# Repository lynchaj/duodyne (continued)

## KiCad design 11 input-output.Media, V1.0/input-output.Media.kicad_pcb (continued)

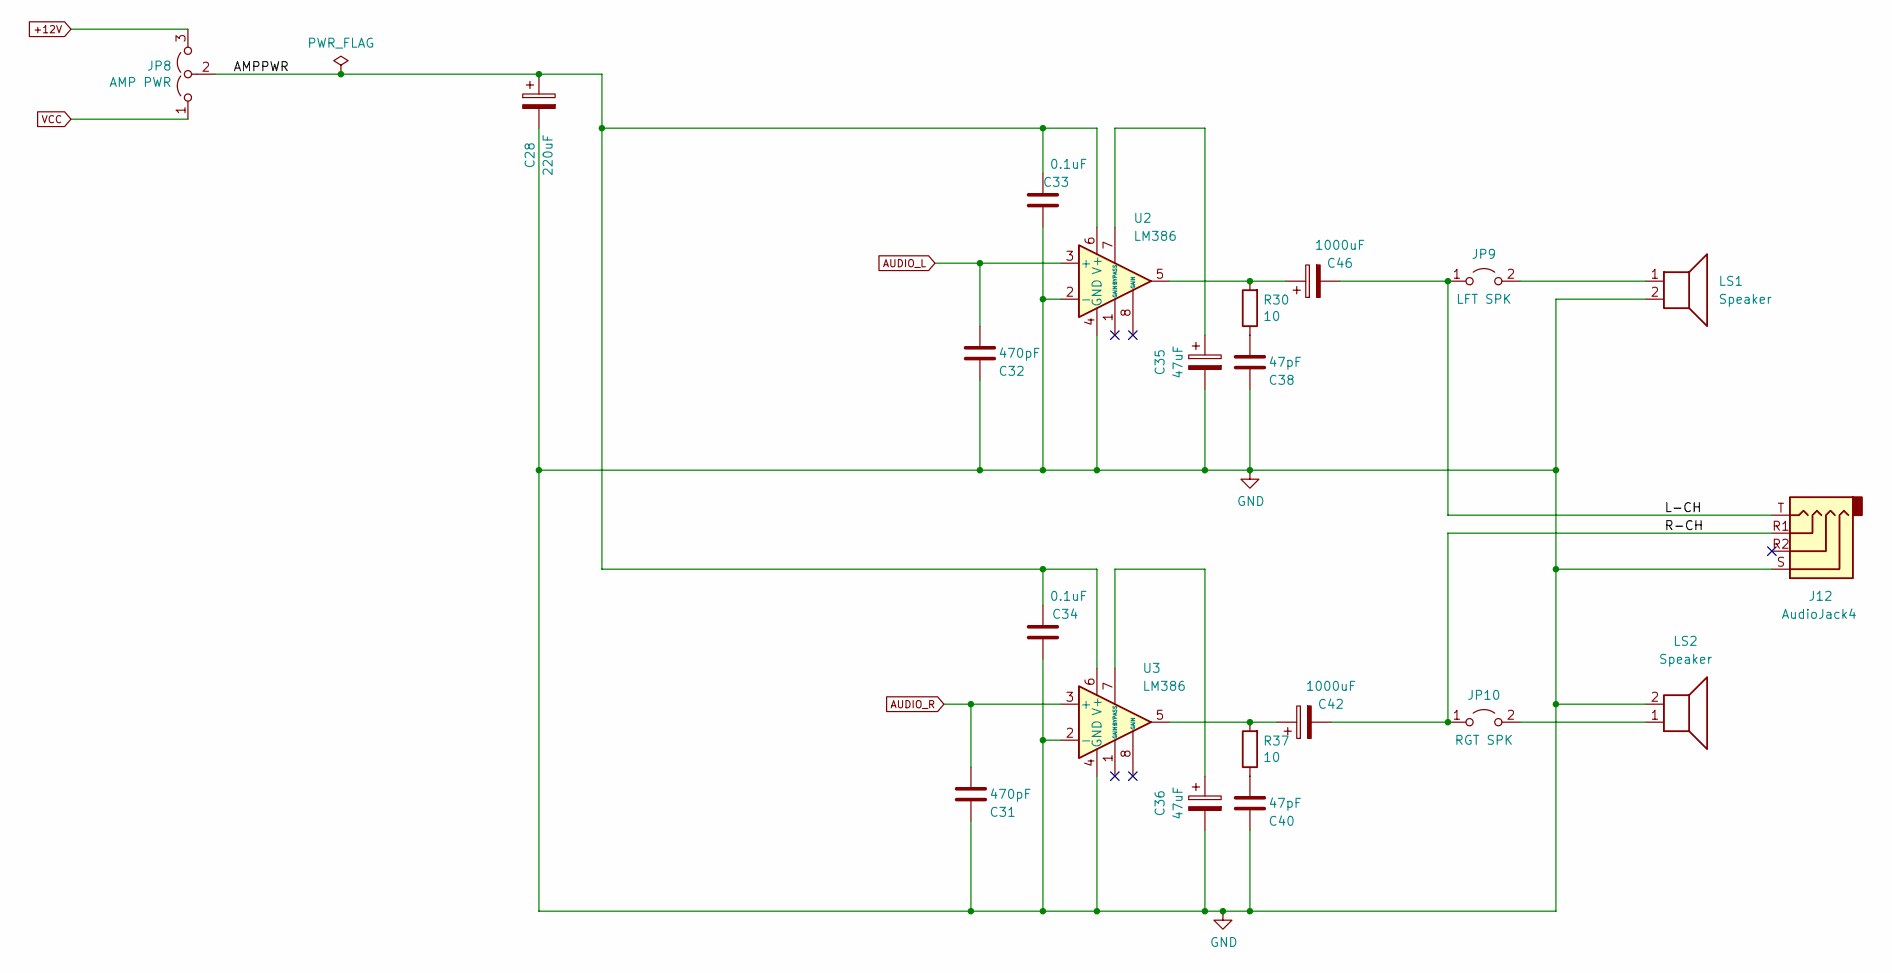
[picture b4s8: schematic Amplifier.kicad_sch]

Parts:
C28: 220uF; CP_Radial_D8.0mm_P2.50mm
C31, C32: 470pF; C_Disc_D3.8mm_W2.6mm_P2.50mm
C33, C34: 0.1uF; C_Disc_D5.0mm_W2.5mm_P5.00mm
C35, C36: 47uF; CP_Radial_D5.0mm_P2.50mm
C38, C40: 47pF; C_Disc_D3.8mm_W2.6mm_P2.50mm
C42, C46: 1000uF; CP_Radial_D8.0mm_P2.50mm
J12: AudioJack4; Jack_3.5mm_PJ320E_Horizontal
JP8: AMP PWR; PinHeader_1x03_P2.54mm_Vertical
JP9: LFT SPK; PinHeader_1x02_P2.54mm_Vertical
JP10: RGT SPK; PinHeader_1x02_P2.54mm_Vertical
LS1, LS2: Speaker; Jameco PCB Speaker 30mm 135722
R30, R37: 10; R_Axial_DIN0207_L6.3mm_D2.5mm_P10.16mm_Horizontal
U2, U3: LM386; DIP-8_W7.62mm

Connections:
+12V: JP8.3 (B); also elsewhere on the board
/Amplifier/AMPPWR: C28.1, C33.2, C34.2, JP8.2 (C), U2.6 (V+), U3.6 (V+)
/Amplifier/L-CH: C46.2, J12.T, JP9.1 (A)
/Amplifier/R-CH: C42.2, J12.R1, JP10.1 (A)
AUDIO_L: C32.1, U2.3 (+); also elsewhere on the board
AUDIO_R: C31.1, U3.3 (+); also elsewhere on the board
GND: C28.2, C31.2, C32.2, C33.1, C34.1, C35.2, C36.2, C38.2, C40.2, J12.S, LS1.2, LS2.2, U2.2 (-), U2.4 (GND), U3.2 (-), U3.4 (GND); also elsewhere on the board
unnamed: C35.1, U2.7 (BYPASS)
unnamed: C36.1, U3.7 (BYPASS)
unnamed: C38.1, R30.1
unnamed: C40.1, R37.1
unnamed: C42.1, R37.2, U3.5
unnamed: C46.1, R30.2, U2.5
unnamed: JP9.2 (B), LS1.1
unnamed: JP10.2 (B), LS2.1
VCC: JP8.1 (A); also elsewhere on the board

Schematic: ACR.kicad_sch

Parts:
D2, D4: LED; LED_D3.0mm_Horizontal_O3.81mm_Z2.0mm
R6, R10: 470; R_Axial_DIN0207_L6.3mm_D2.5mm_P7.62mm_Horizontal
U4: 74LS06; DIP-14_W7.62mm
U9: 74LS174; DIP-16_W7.62mm
U24: 74LS04; DIP-14_W7.62mm

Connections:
/ACR/STATUS-PSG: U4.11, U9.10 (Q3)
/ACR/STATUS-VDP: U4.3, U9.7 (Q2)
ACR5: U9.15 (Q5); also elsewhere on the board
GND: U9.8 (GND); also elsewhere on the board
unnamed: D2.1 (K), U4.4
unnamed: D2.2 (A), R6.1
unnamed: D4.1 (K), U4.10
unnamed: D4.2 (A), R10.1
unnamed: U9.2 (Q0), U24.5
VCC: R6.2, R10.2, U9.16 (VCC); also elsewhere on the board
bD0: U9.3 (D0); also elsewhere on the board
bD1: U9.4 (D1); also elsewhere on the board
bD2: U9.6 (D2); also elsewhere on the board
bD3: U9.11 (D3); also elsewhere on the board
bD4: U9.13 (D4); also elsewhere on the board
bD5: U9.14 (D5); also elsewhere on the board
~CS_ACR_WR: U9.9 (Cp); also elsewhere on the board
~RESAY3: U9.12 (Q4); also elsewhere on the board
~RESVDP: U24.6; also elsewhere on the board
~bRESET: U9.1 (~Mr); also elsewhere on the board

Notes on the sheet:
NOTE: ~{RESVDP} DEFAULTS TO HIGH LATCH Q0 MUST BE SET TO HIGH TO RESET V9938 OR V9958 (bD0=1)

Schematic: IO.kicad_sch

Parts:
RN1: 10K; R_Array_SIP9
SW1: IO PORT ADDR; PinHeader_2x05_P2.54mm_Vertical
U21: 74LS688; DIP-20_W7.62mm

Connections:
GND: U21.10 (GND); also elsewhere on the board
unnamed: RN1.2 (R1), SW1.1, U21.18 (R7)
unnamed: RN1.3 (R2), SW1.3, U21.16 (R6)
unnamed: RN1.4 (R3), SW1.5, U21.14 (R5)
unnamed: RN1.5 (R4), SW1.7, U21.12 (R4)
unnamed: RN1.6 (R5), SW1.9, U21.9 (R3)
unnamed: RN1.9 (R8), U21.3 (R0), U21.4 (P1), U21.5 (R1), U21.6 (P2), U21.7 (R2)
VCC: RN1.1 (common), U21.20 (VCC); also elsewhere on the board
ZERO: SW1.2, SW1.4, SW1.6, SW1.8, SW1.10; also elsewhere on the board
bA3: U21.8 (P3); also elsewhere on the board
bA4: U21.11 (P4); also elsewhere on the board
bA5: U21.13 (P5); also elsewhere on the board
bA6: U21.15 (P6); also elsewhere on the board
bA7: U21.17 (P7); also elsewhere on the board
~CS_MEDIA: U21.19 (P=R); also elsewhere on the board
~bIORQ: U21.1 (G); also elsewhere on the board
~bM1: U21.2 (P0); also elsewhere on the board

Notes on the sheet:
SET IO PORT
Note: IO Address Port $A0-$A7 1-2 =off - A7 (high) 3-4 =on - A6 (low) 5-6 =on - A5 (low) 7-8 =off - A4 (high) 9-10 =on - A3 (low)
IO SELECTION CIRCUIT
Note: Inhibit Board Operation During Interrupts ~{M1} = low, ~{IORQ} = low

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
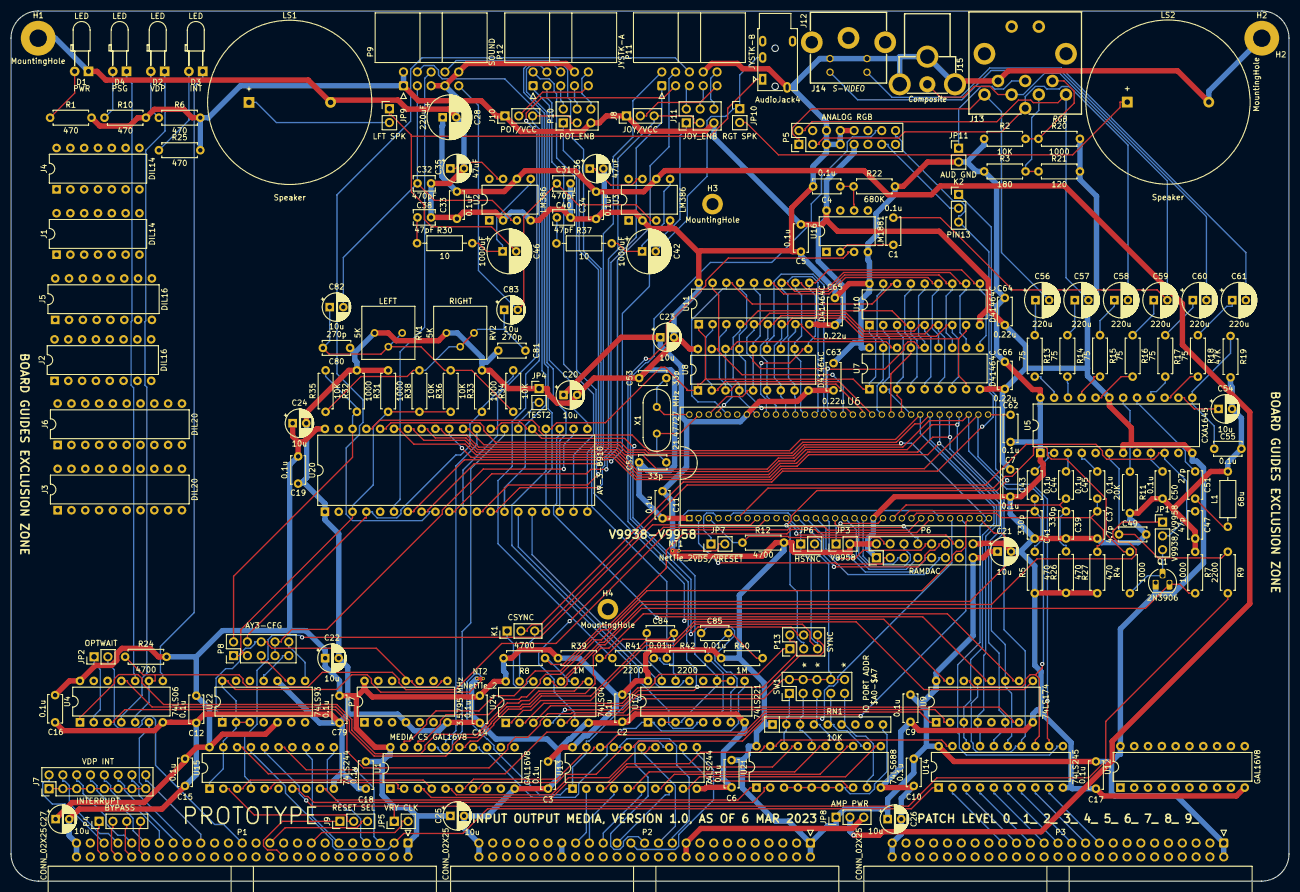
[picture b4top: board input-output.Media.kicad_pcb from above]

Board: 2 copper layers, 235.0 x 160.0 mm, 188 parts (0 on the bottom side), 237 nets.

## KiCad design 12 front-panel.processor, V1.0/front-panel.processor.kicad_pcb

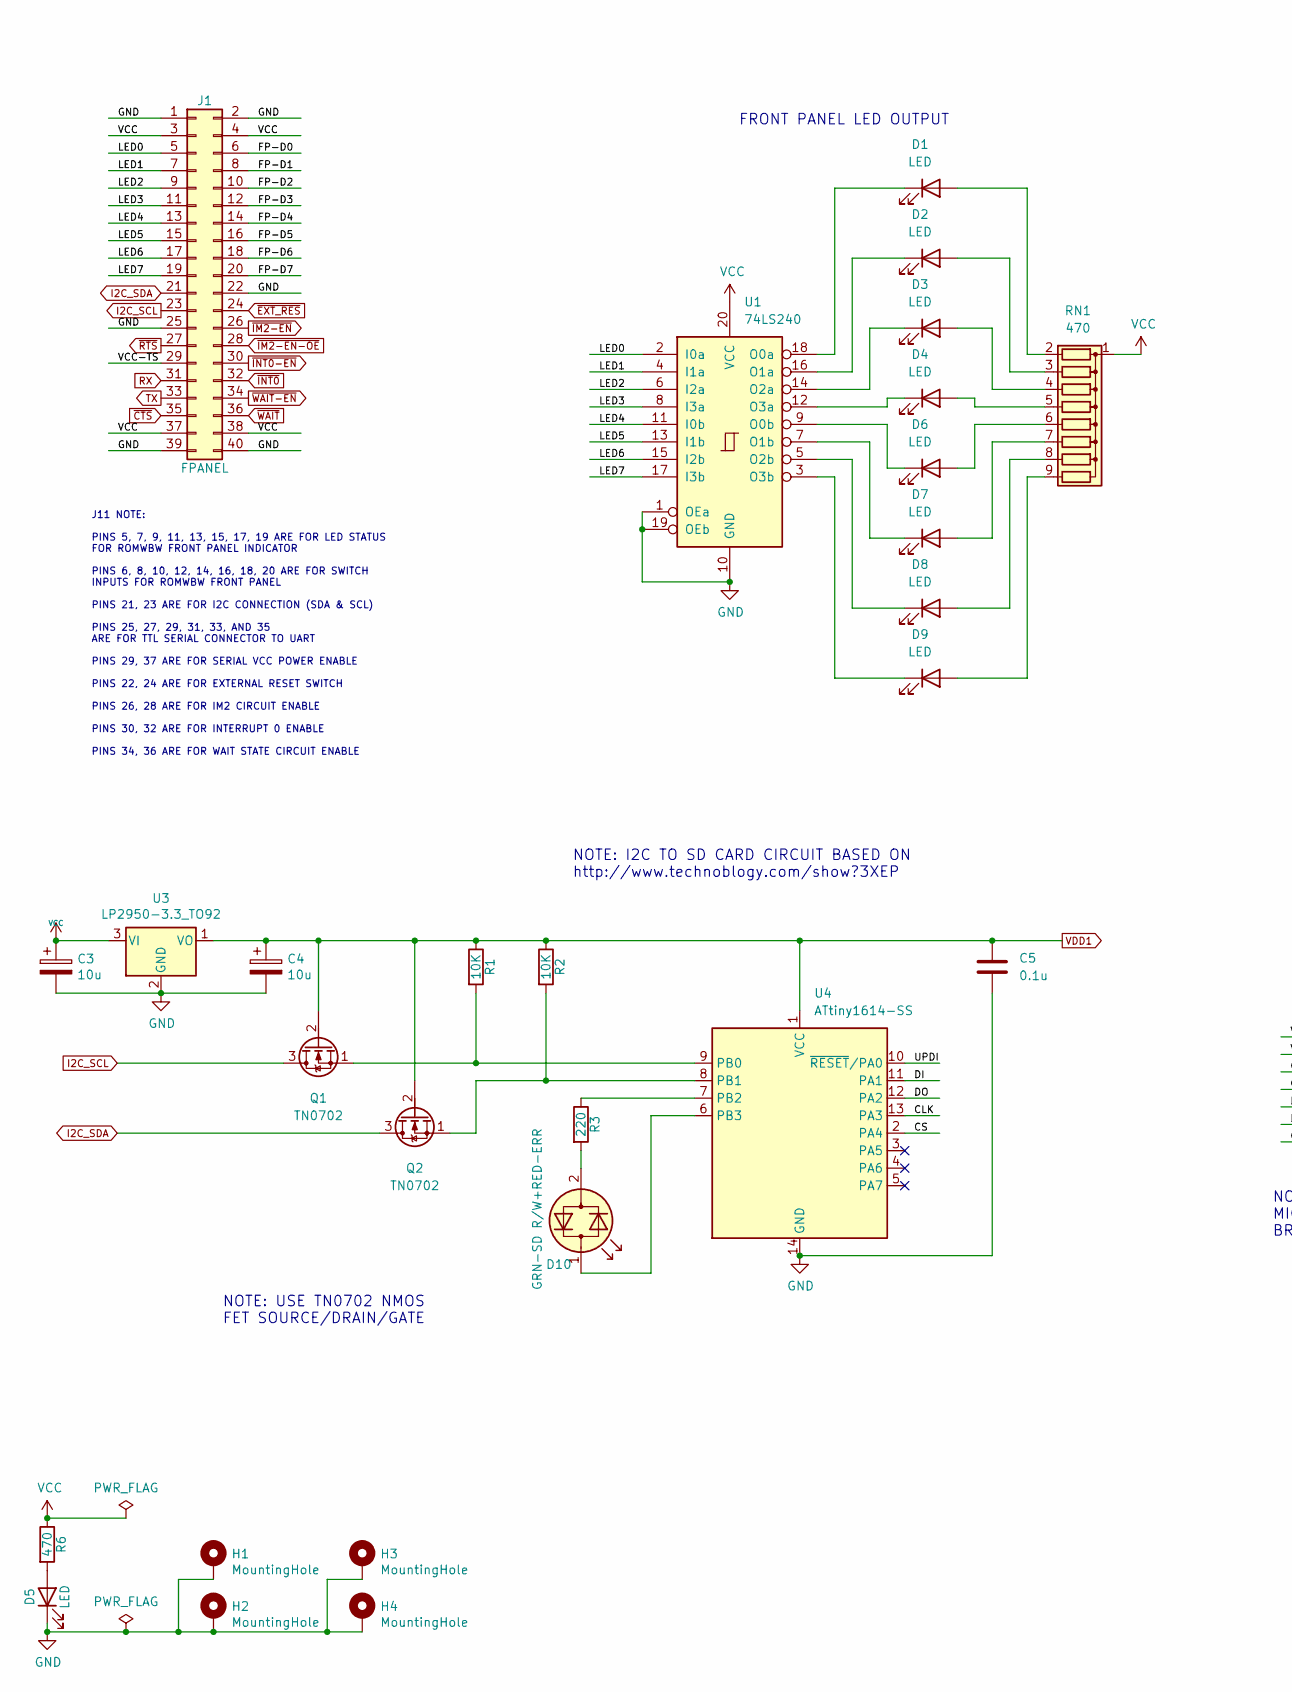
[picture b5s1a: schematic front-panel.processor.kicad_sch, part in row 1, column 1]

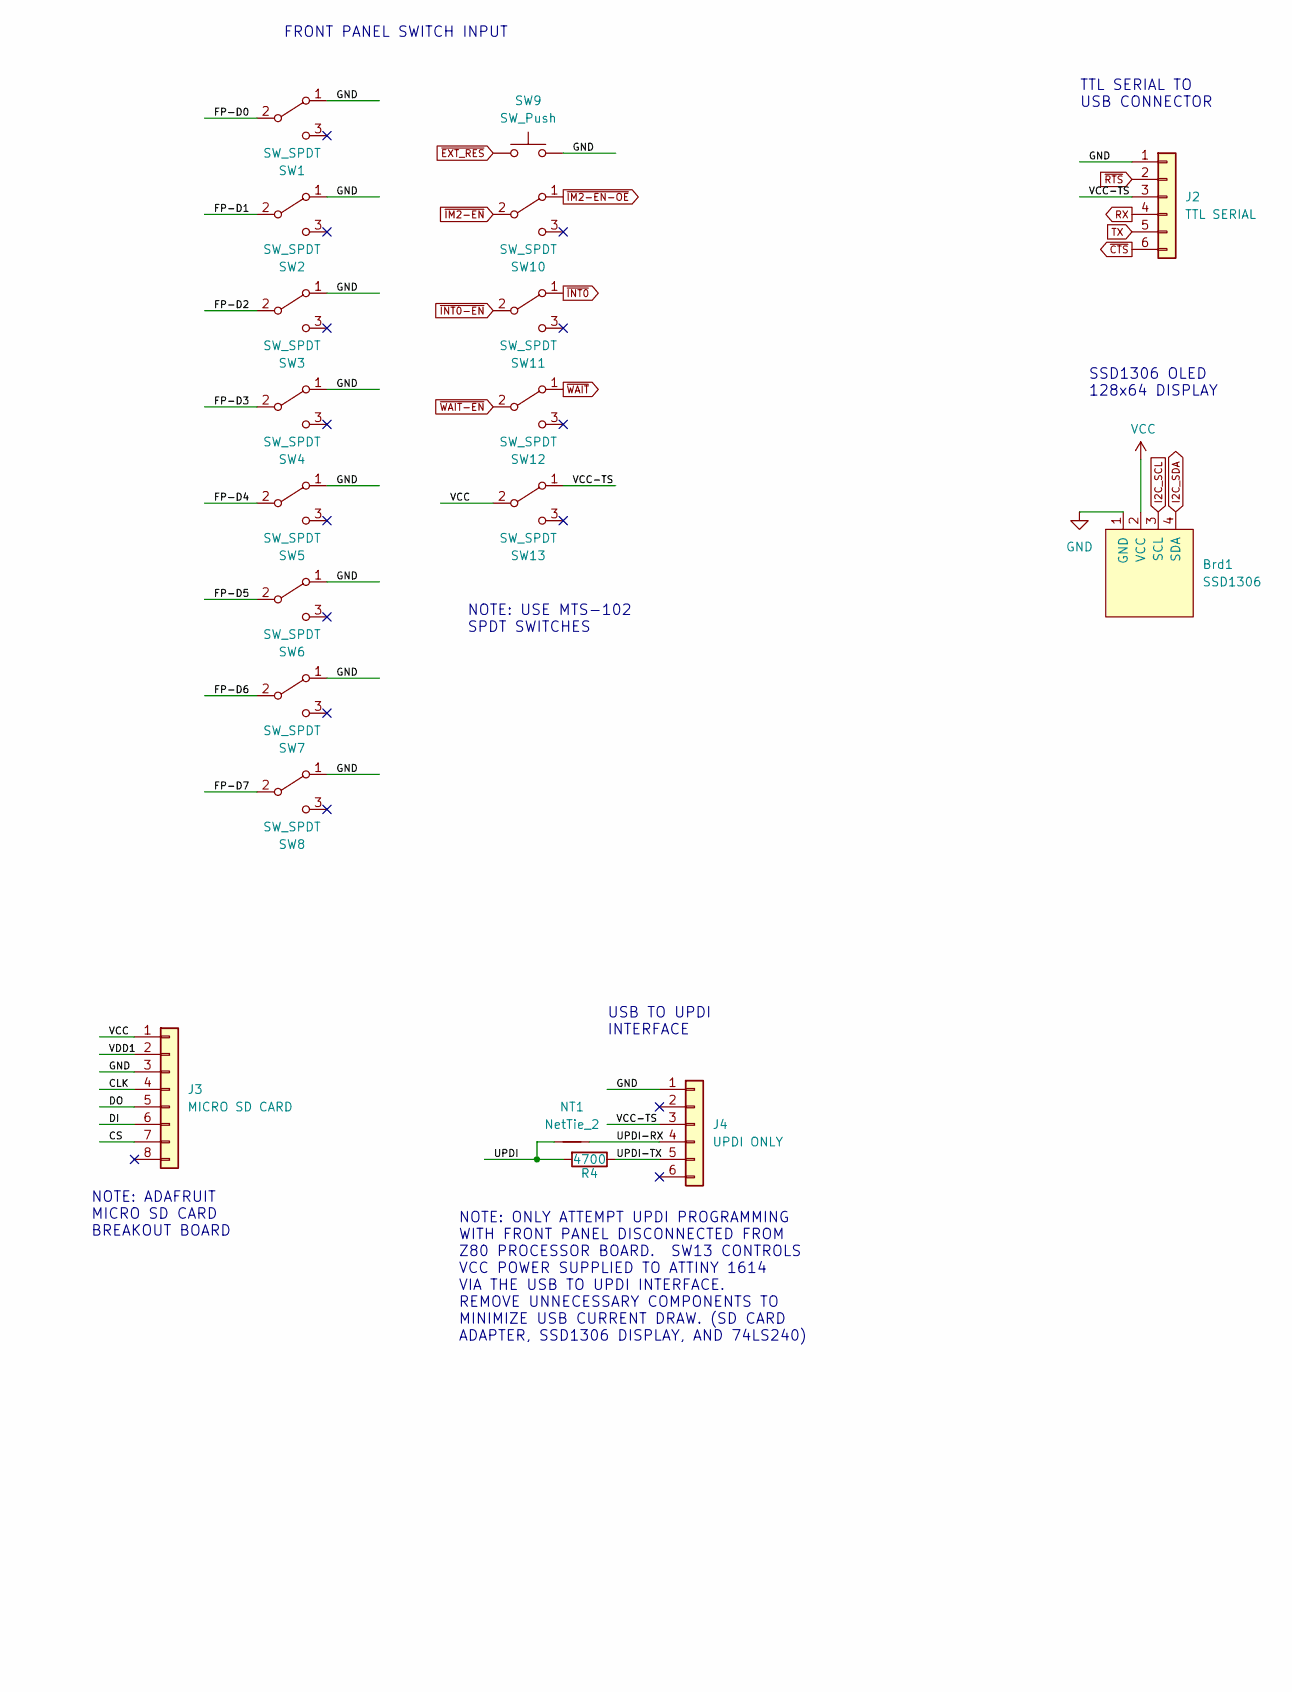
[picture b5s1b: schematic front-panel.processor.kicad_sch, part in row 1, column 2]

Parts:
Brd1: SSD1306; 128x64OLED
C3, C4: 10u; CP_Radial_D5.0mm_P2.50mm
C5: 0.1u; C_Disc_D5.0mm_W2.5mm_P5.00mm
D1, D2, D3, D4, D5, D6, D7, D8, D9: LED; LED_D3.0mm
D10: GRN-SD R/W+RED-ERR; LED_D5.0mm
H1, H2, H3, H4: MountingHole; MountingHole_3.2mm_M3_Pad
J1: FPANEL; IDC-Header_2x20_P2.54mm_Horizontal
J2: TTL SERIAL; PinHeader_1x06_P2.54mm_Vertical
J3: MICRO SD CARD; PinSocket_1x08_P2.54mm_Vertical
J4: UPDI ONLY; PinHeader_1x06_P2.54mm_Vertical
NT1: NetTie_2; NetTie-2_THT_Pad0.3mm
Q1, Q2: TN0702; TO-92_HandSolder
R1, R2: 10K; R_Axial_DIN0207_L6.3mm_D2.5mm_P7.62mm_Horizontal
R3: 220; R_Axial_DIN0207_L6.3mm_D2.5mm_P7.62mm_Horizontal
R4: 4700; R_Axial_DIN0207_L6.3mm_D2.5mm_P7.62mm_Horizontal
R6: 470; R_Axial_DIN0207_L6.3mm_D2.5mm_P7.62mm_Horizontal
RN1: 470; R_Array_SIP9
SW1, SW2, SW3, SW4, SW5, SW6, SW7, SW8, SW10, SW11, SW12, SW13: SW_SPDT; SW_Toggle_Blue_wSlots
SW9: SW_Push; SW_PUSH_6mm
U1: 74LS240; DIP-20_W7.62mm
U3: LP2950-3.3_TO92; TO-92_HandSolder
U4: ATtiny1614-SS; SOIC-14_3.9x8.7mm_P1.27mm

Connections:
/CLK: J3.4, U4.13 (PA3)
/CS: J3.7, U4.2 (PA4)
/DI: J3.6, U4.11 (PA1)
/DO: J3.5, U4.12 (PA2)
/FP-D0: J1.6, SW1.2 (B)
/FP-D1: J1.8, SW2.2 (B)
/FP-D2: J1.10, SW3.2 (B)
/FP-D3: J1.12, SW4.2 (B)
/FP-D4: J1.14, SW5.2 (B)
/FP-D5: J1.16, SW6.2 (B)
/FP-D6: J1.18, SW7.2 (B)
/FP-D7: J1.20, SW8.2 (B)
/LED0: J1.5, U1.2 (I0a)
/LED1: J1.7, U1.4 (I1a)
/LED2: J1.9, U1.6 (I2a)
/LED3: J1.11, U1.8 (I3a)
/LED4: J1.13, U1.11 (I0b)
/LED5: J1.15, U1.13 (I1b)
/LED6: J1.17, U1.15 (I2b)
/LED7: J1.19, U1.17 (I3b)
/UPDI: NT1.2, R4.2, U4.10 (~RESET/PA0)
/UPDI-RX: J4.4, NT1.1
/UPDI-TX: J4.5, R4.1
/VCC-TS: J1.29, J2.3, J4.3, SW13.1 (A)
GND: Brd1.1 (GND), C3.2, C4.2, C5.1, D5.1 (K), H1.1, H2.1, H3.1, H4.1, J1.1, J1.2, J1.22, J1.25, J1.39, J1.40, J2.1, J3.3, J4.1, SW1.1 (A), SW2.1 (A), SW3.1 (A), SW4.1 (A), SW5.1 (A), SW6.1 (A), SW7.1 (A), SW8.1 (A), SW9.2, U1.1 (OEa), U1.10 (GND), U1.19 (OEb), U3.2 (GND), U4.14 (GND)
I2C_SCL: Brd1.3 (SCL), J1.23, Q1.3 (D)
I2C_SDA: Brd1.4 (SDA), J1.21, Q2.3 (D)
unnamed: D1.1 (K), U1.18 (O0a)
unnamed: D1.2 (A), RN1.2 (R1)
unnamed: D2.1 (K), U1.16 (O1a)
unnamed: D2.2 (A), RN1.3 (R2)
unnamed: D3.1 (K), U1.14 (O2a)
unnamed: D3.2 (A), RN1.4 (R3)
unnamed: D4.1 (K), U1.12 (O3a)
unnamed: D4.2 (A), RN1.5 (R4)
unnamed: D5.2 (A), R6.2
unnamed: D6.1 (K), U1.9 (O0b)
unnamed: D6.2 (A), RN1.6 (R5)
unnamed: D7.1 (K), U1.7 (O1b)
unnamed: D7.2 (A), RN1.7 (R6)
unnamed: D8.1 (K), U1.5 (O2b)
unnamed: D8.2 (A), RN1.8 (R7)
unnamed: D9.1 (K), U1.3 (O3b)
unnamed: D9.2 (A), RN1.9 (R8)
unnamed: D10.1 (KA), U4.6 (PB3)
unnamed: D10.2 (AK), R3.2
unnamed: Q1.1 (S), R1.2, U4.9 (PB0)
unnamed: Q2.1 (S), R2.2, U4.8 (PB1)
unnamed: R3.1, U4.7 (PB2)
RX: J1.31, J2.4
TX: J1.33, J2.5
VCC: Brd1.2 (VCC), C3.1, J1.3, J1.4, J1.37, J1.38, J3.1, R6.1, RN1.1 (common), SW13.2 (B), U1.20 (VCC), U3.3 (VI)
VDD1: C4.1, C5.2, J3.2, Q1.2 (G), Q2.2 (G), R1.1, R2.1, U3.1 (VO), U4.1 (VCC)
~CTS: J1.35, J2.6
~EXT_RES: J1.24, SW9.1
~IM2-EN-OE: J1.28, SW10.1 (A)
~IM2-EN: J1.26, SW10.2 (B)
~INT0-EN: J1.30, SW11.2 (B)
~INT0: J1.32, SW11.1 (A)
~RTS: J1.27, J2.2
~WAIT-EN: J1.34, SW12.2 (B)
~WAIT: J1.36, SW12.1 (A)

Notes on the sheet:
SSD1306 OLED 128x64 DISPLAY
FRONT PANEL LED OUTPUT
NOTE: USE TN0702 NMOS FET SOURCE/DRAIN/GATE
J11 NOTE: PINS 5, 7, 9, 11, 13, 15, 17, 19 ARE FOR LED STATUS FOR ROMWBW FRONT PANEL INDICATOR PINS 6, 8, 10, 12, 14, 16, 18, 20 ARE FOR SWITCH INPUTS FOR ROMWBW FRONT PANEL PINS 21, 23 ARE FOR I2C CONNECTION (SDA & SCL) PINS 25, 27, 29, 31, 33, AND 35 ARE FOR TTL SERIAL CONNECTOR TO UART PINS 29, 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
NOTE: ADAFRUIT MICRO SD CARD BREAKOUT BOARD
USB TO UPDI INTERFACE
NOTE: USE MTS-102 SPDT SWITCHES
NOTE: I2C TO SD CARD CIRCUIT BASED ON http://www.technoblogy.com/show?3XEP
NOTE: ONLY ATTEMPT UPDI PROGRAMMING WITH FRONT PANEL DISCONNECTED FROM Z80 PROCESSOR BOARD. SW13 CONTROLS VCC POWER SUPPLIED TO ATTINY 1614 VIA THE USB TO UPDI INTERFACE. REMOVE UNNECESSARY COMPONENTS TO MINIMIZE USB CURRENT DRAW. (SD CARD ADAPTER, SSD1306 DISPLAY, AND 74LS240)
FRONT PANEL SWITCH INPUT
TTL SERIAL TO USB CONNECTOR

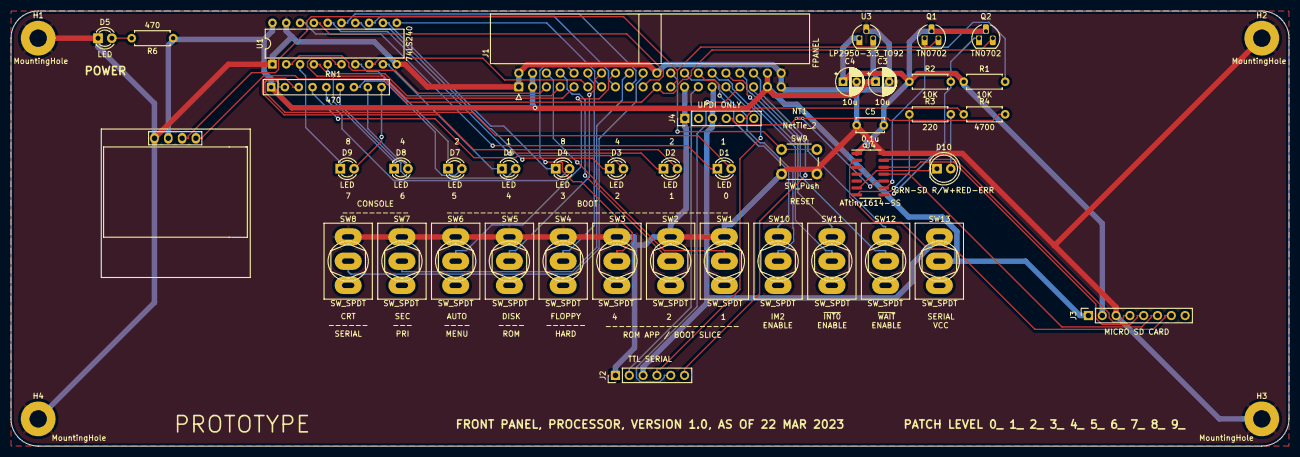
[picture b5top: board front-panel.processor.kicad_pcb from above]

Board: 2 copper layers, 235.0 x 80.0 mm, 47 parts (0 on the bottom side), 62 nets.
